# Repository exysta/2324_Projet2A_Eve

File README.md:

# Project Eve

<div align="center">

<br>

[Code](Code/) 
| [Documentation](Documents/) 
| [Liens utiles](Documents/Liens_utiles.md) 
| [Journal](Journal/ReadMe.md)
| [Bilan des présentations](Présentation/ReadMe.md)

</div>

## Introduction

Vous vous situez sur le Github d'Eve (anciennement Robourt). C'est un projet de bras robotique six axes réalisé par des étudiants de l'ENSEA. Vous pourrez trouver ici la documentation, le guide d'utilisation, le journal de bord (et autres documents connexes) pour comprendre notre projet. Nous vous souhaitons une bonne lecture !

> You are in the Github of Eve (formely Robourt). This is a project of a six-axis robot arm project by students at ENSEA. Here you can find here documentation, user guide, logbook (and other related documents) to help you understand our project. We hope you enjoy reading! The rest of the text will be in French exclusively.

### Table des matières

1. [Partie Software](#partie-software)
2. [Partie Hardware et intégration](#partie-hardware-et-intégration)
3. [Guide d'utilisation](#guide-dutilisation)
4. [Annexes](#annexes)

## Partie-Software

### Contrôle des servos moteurs avec Dynamixel 2.0

Dans le cadre du projet, les servomoteurs servent à actionner la pince et à gérer certains axes de rotation du robot ne nécessitant pas beaucoup de couple. Il y a un total de 4 servomoteurs, tous utilisant le protocole Dynamixel 2.0 et connectés en série. Nous utilisons une connexion UART en mode half-duplex avec notre microprocesseur.

#### Connexion UART Half-Duplex

Il est nécessaire de configurer le GPIO utilisé pour l'UART en mode open drain avec une résistance de pull-up pour que le half-duplex puisse fonctionner.
<div align="center">
<br>
 </br>
Extrait du reference manual </br>
</br> 
</div>

Pour envoyer et recevoir des données, il est nécessaire de préciser si l'on transmet ou reçoit pour éviter les conflits sur le fil unique utilisé pour l'UART. Pour cela, on utilise les fonctions HAL correspondantes HAL_HalfDuplex_EnableTransmitter() et HAL_HalfDuplex_EnableReceiver().

#### Protocole Dynamixel 2.0

La majorité des informations ont été obtenues sur cette page https://emanual.robotis.com/docs/en/dxl/protocol2/

### Contrôle des steppers par la TMC2590

#### Connexion SPI

On doit configurer SPI1 avec 3 ports MISO/MOSI & CLK (configurable dans IOC) et un Chip Select Not. Pour asservir un driver, il faut mettre son bit en état bas (ce qui a été fait dans l'initialisation du code).
Le but est de transmettre un mot en bits contenant l'ordre (angles en degré) et la configuration du TMC2590. 

Pour cela nous avons la possibilité d'écrire dans 5 registres différents

<div align="center">
<br>
 </br>
Registres </br>
</br> 
</div>

<div align="center">
<br>
 </br>
Formats des registres </br>
</br> 
</div>

On remarque alors que ce sont les 2 bits de poids fort qui détermine dans quels registres nous écrivons.  Nous modifierons uniquement 2 registres : DRVCTRL & DRVCON. Nous laisserons les autres registres aux valeurs par défaut (mais nous pourrons les configurer à besoin si nécessaire).

##### Registre DRVCTRL

C'est le registre qui fait décide du courant à envoyer dans le stepper.

<div align="center">
<br>
 </br>
Formats du registre DRVCTRL en mode SPI </br>
</br> 
</div>

Pour commander les steppers, il faut leur envoyer des amplitudes de courant. Il faut donc trouver une relation entre les angles et le courant. Nous avons trouvé une relation entre les deux avec un sinus. __A expliquer__

On sait que le courant correspond à la partie entière du sinus(angle) * 255. On stocke ensuite toutes ces données dans un tableau qui fait des ordres de 0 à 90°. Comme le sinus est périodique, cela suffira à faire n'importe quel calcul de sinus/cosinus.

##### Registre DRVCONF

C'est le registre qui configure le driver.

<div align="center">
<br>
 </br>
Formats du registre DRVCONF </br>
</br> 
</div>

C'est ici qu'il faut modfier le bit pour désactiver l'interface STEP/DIR. Pour choisir le mode SPI il faut que le bit SDOFF soit égal à 1. Sinon, l'interface choisie sera STEP/DIR.

Il faudra aussi modifier les bits 4&5 pour configurer une partie de la réponse (voir image suivante).

##### Les registres pour la réponse

Nous pouvons aussi récupérer des informations à l'aide d'autres registres uniquement en lecture.

<div align="center">
<br>
 </br>
Formats des registres de réponse </br>
</br> 
</div>

Nous avons donc configuré les registres avec les paramètres suivants :

```c
	phtmc2590->drvCtrlRegister 			= 0x00000; // No Current
	phtmc2590->chopConfRegister			= 0b10011000000000001111; // 100 10
	phtmc2590->smartEnRegister 			= 0b10100000000000000000; // 101 0
	phtmc2590->stallGuardCtrlRegister 	= 0b11000000000000011111;//0xD001F; // 110 1---- 11111
	phtmc2590->drvConfRegister 			= 0b11100000011110110000;//0xE0480; // 1110 0000 0100 1000 0000
```

#### Explication du code

Nous sommes passé par une structure
Le code de commande pour la TMC2590 est séparé en plusieurs parties : 

* tmc2590_Init : Permet d'initialiser les registres du driver et de le mettre prêt au fonctionnement. Pour le moment, l'activation du signal nCS se fait à ce moment mais par la suite, il sera fait dans une autre fonction qui décidera avec quel stepper on communique.

```c
void tmc2590_Init(TMC2590_HandleTypeDef *phtmc2590, SPI_HandleTypeDef *hspi, GPIO_TypeDef *gpioPortNCS, uint16_t gpioPinNCS, GPIO_TypeDef *gpioPortDrvEnN, uint16_t gpioPinDrvEnN){
	uint8_t pData[3];
	phtmc2590->hspi = hspi;
	phtmc2590->gpioPinNCS = gpioPinNCS;
	phtmc2590->gpioPortNCS = gpioPortNCS;
	phtmc2590->gpioPinDrvEnN = gpioPinDrvEnN;
	phtmc2590->gpioPortDrvEnN = gpioPortDrvEnN;

	tmc2590_SetPowerEnable(phtmc2590, SET);
	tmc2590_SetnCS(phtmc2590, SET);

	phtmc2590->drvCtrlRegister 			= 0x00000; // No Current
	phtmc2590->chopConfRegister			= 0b10011000000000001111; // 100 10
	phtmc2590->smartEnRegister 			= 0b10100000000000000000; // 101 0
	phtmc2590->stallGuardCtrlRegister 	= 0b11000000000000011111;//0xD001F; // 110 1---- 11111
	phtmc2590->drvConfRegister 			= 0b11100000011110110000;//0xE0480; // 1110 0000 0100 1000 0000

	tmc2590_SetTxBufferInt32(phtmc2590, phtmc2590->drvCtrlRegister);
	tmc2590_TransmitReceive(phtmc2590, TMC2590_CMD_SIZE);
	tmc2590_SetTxBufferInt32(phtmc2590, phtmc2590->chopConfRegister);
	tmc2590_TransmitReceive(phtmc2590, TMC2590_CMD_SIZE);
	tmc2590_SetTxBufferInt32(phtmc2590, phtmc2590->smartEnRegister);
	tmc2590_TransmitReceive(phtmc2590, TMC2590_CMD_SIZE);
	tmc2590_SetTxBufferInt32(phtmc2590, phtmc2590->stallGuardCtrlRegister);
	tmc2590_TransmitReceive(phtmc2590, TMC2590_CMD_SIZE);
	tmc2590_SetTxBufferInt32(phtmc2590, phtmc2590->drvConfRegister);
	tmc2590_TransmitReceive(phtmc2590, TMC2590_CMD_SIZE);

	HAL_TIM_Base_Start_IT(&htim2);

}
```
<div align="center">
Code tmc2590_Init </br>
</br> 
</div>

Entrées : 
* Structure TMC2590
* Pointeur SPI
* Signal nCS
* Pin nCS
* Signal DRVENN
* Pin DRVENN

* sendOrderStepper : 

```c
int sendOrderStepper(int inputOrder){

	/*
	 * We need to put in input how much we want to turn in degrees and what stepper we want to move
	 * For the moment, we have only one stepper but with nCS signal, we will be able to change with
	 * stepper we want to communicate
	 */
	int polarity = (inputOrder>0);
	int order = (int) abs(inputOrder)*142.2;
	int indice = 0;
	while (indice != order){
		uint32_t stateInterruption = HAL_GPIO_ReadPin(GPIOC, GPIO_PIN_8);
		if (stateInterruption != 0){
			return 0;
		}
		if(perioedElapsed_IT){
				if(index_sin_loop < 256){
					currentCoilA = sinTable[index_sin_loop];
					currentCoilB = sinTable[256-index_sin_loop];
					polarityCoilA = polarity;
					polarityCoilB = 1;
				}
				else if(index_sin_loop < 512){
					currentCoilA = sinTable[512-index_sin_loop];
					currentCoilB = sinTable[index_sin_loop-256];
					polarityCoilA = polarity;
					polarityCoilB = 0;
				}
				else if(index_sin_loop < 768){
					currentCoilA = sinTable[index_sin_loop-512];
					currentCoilB = sinTable[768-index_sin_loop];
					polarityCoilA = 1 - polarity;
					polarityCoilB = 0;
				}
				else{
					currentCoilA = sinTable[1024-index_sin_loop];
					currentCoilB = sinTable[index_sin_loop-768];
					polarityCoilA = 1 - polarity;
					polarityCoilB = 1;
				}
				index_sin_loop = (index_sin_loop+1)%1024;
				indice++;

				drvCtrlCommand = (polarityCoilA << 17) | (currentCoilA << 9) | (polarityCoilB << 8) | (currentCoilB << 0);
				tmc2590_SetTxBufferInt32(&htmc2590, drvCtrlCommand);
				tmc2590_TransmitReceive(&htmc2590, TMC2590_CMD_SIZE);
				perioedElapsed_IT = 0;
			}
	}
	return 1;

```

<div align="center">
Code sendOrderStepper </br>
</div>

### ROS 2

Il y a deux manières de faire avec ROS2 :
* ROS2 contrôle tout : le contrôle, la gestion des ressources et les calculs => Utilisation de [ROS_Control](https://github.com/ros-controls/control.ros.org) (Méthode 1)
* ROS2 ne fait presque rien : Il transmet simplement les données d'un point A à un point B (Méthode 2)

<div align="center">
<br>
 </br>
Schéma de la méthode 1 </br>
</br> 
</div>

Le problème avec la méthode 1, c'est que comme tout est géré par ROS, on n'utilise pas la STM32 et donc notre projet d'électronique n'a plus de sens. Autre problème de la méthode 1, c'est l'utilisation de C++ pour faire le code qui est un langage POO assez complexe à prendre en main alors que tous les packages étaient actuellement fait sous python.

La 2e méthode revient à créer une entrée où l'on mettra les ordres (des angles pour différents moteurs) puis tout est envoyé par UART à la STM32 qui effectue l'envoi des ordre pour chacun des moteurs. 

C'est plutôt la 2e méthode qui est envisagée étant donnée que le groupe de 3e année ont réalisé une simulation qui permet de passer de coordonnées x,y & z en données d'angles pour chaque moteur. On aurait alors à transmettre ces données à la carte STM32 (UART) qui s'occuperait de la partie commande des moteurs.

Il faut définir le protocole de communication entre les deux appareils en s'inspirant du Dynamixel.

## Partie Hardware et intégration

### Cahier des charges - Matériel

* TMC2590
* 17hs19-2004s
* XL320 (x2)
* XL430 w250 (x2)
* 23HS8430
* 23hS2442B Nema 23
* STM32 L412
* BU33SD5WG-TR

<div align="center">

</div>

## Annexes

Diagramme de Gantt

<div align="center">
 </br>
</div>

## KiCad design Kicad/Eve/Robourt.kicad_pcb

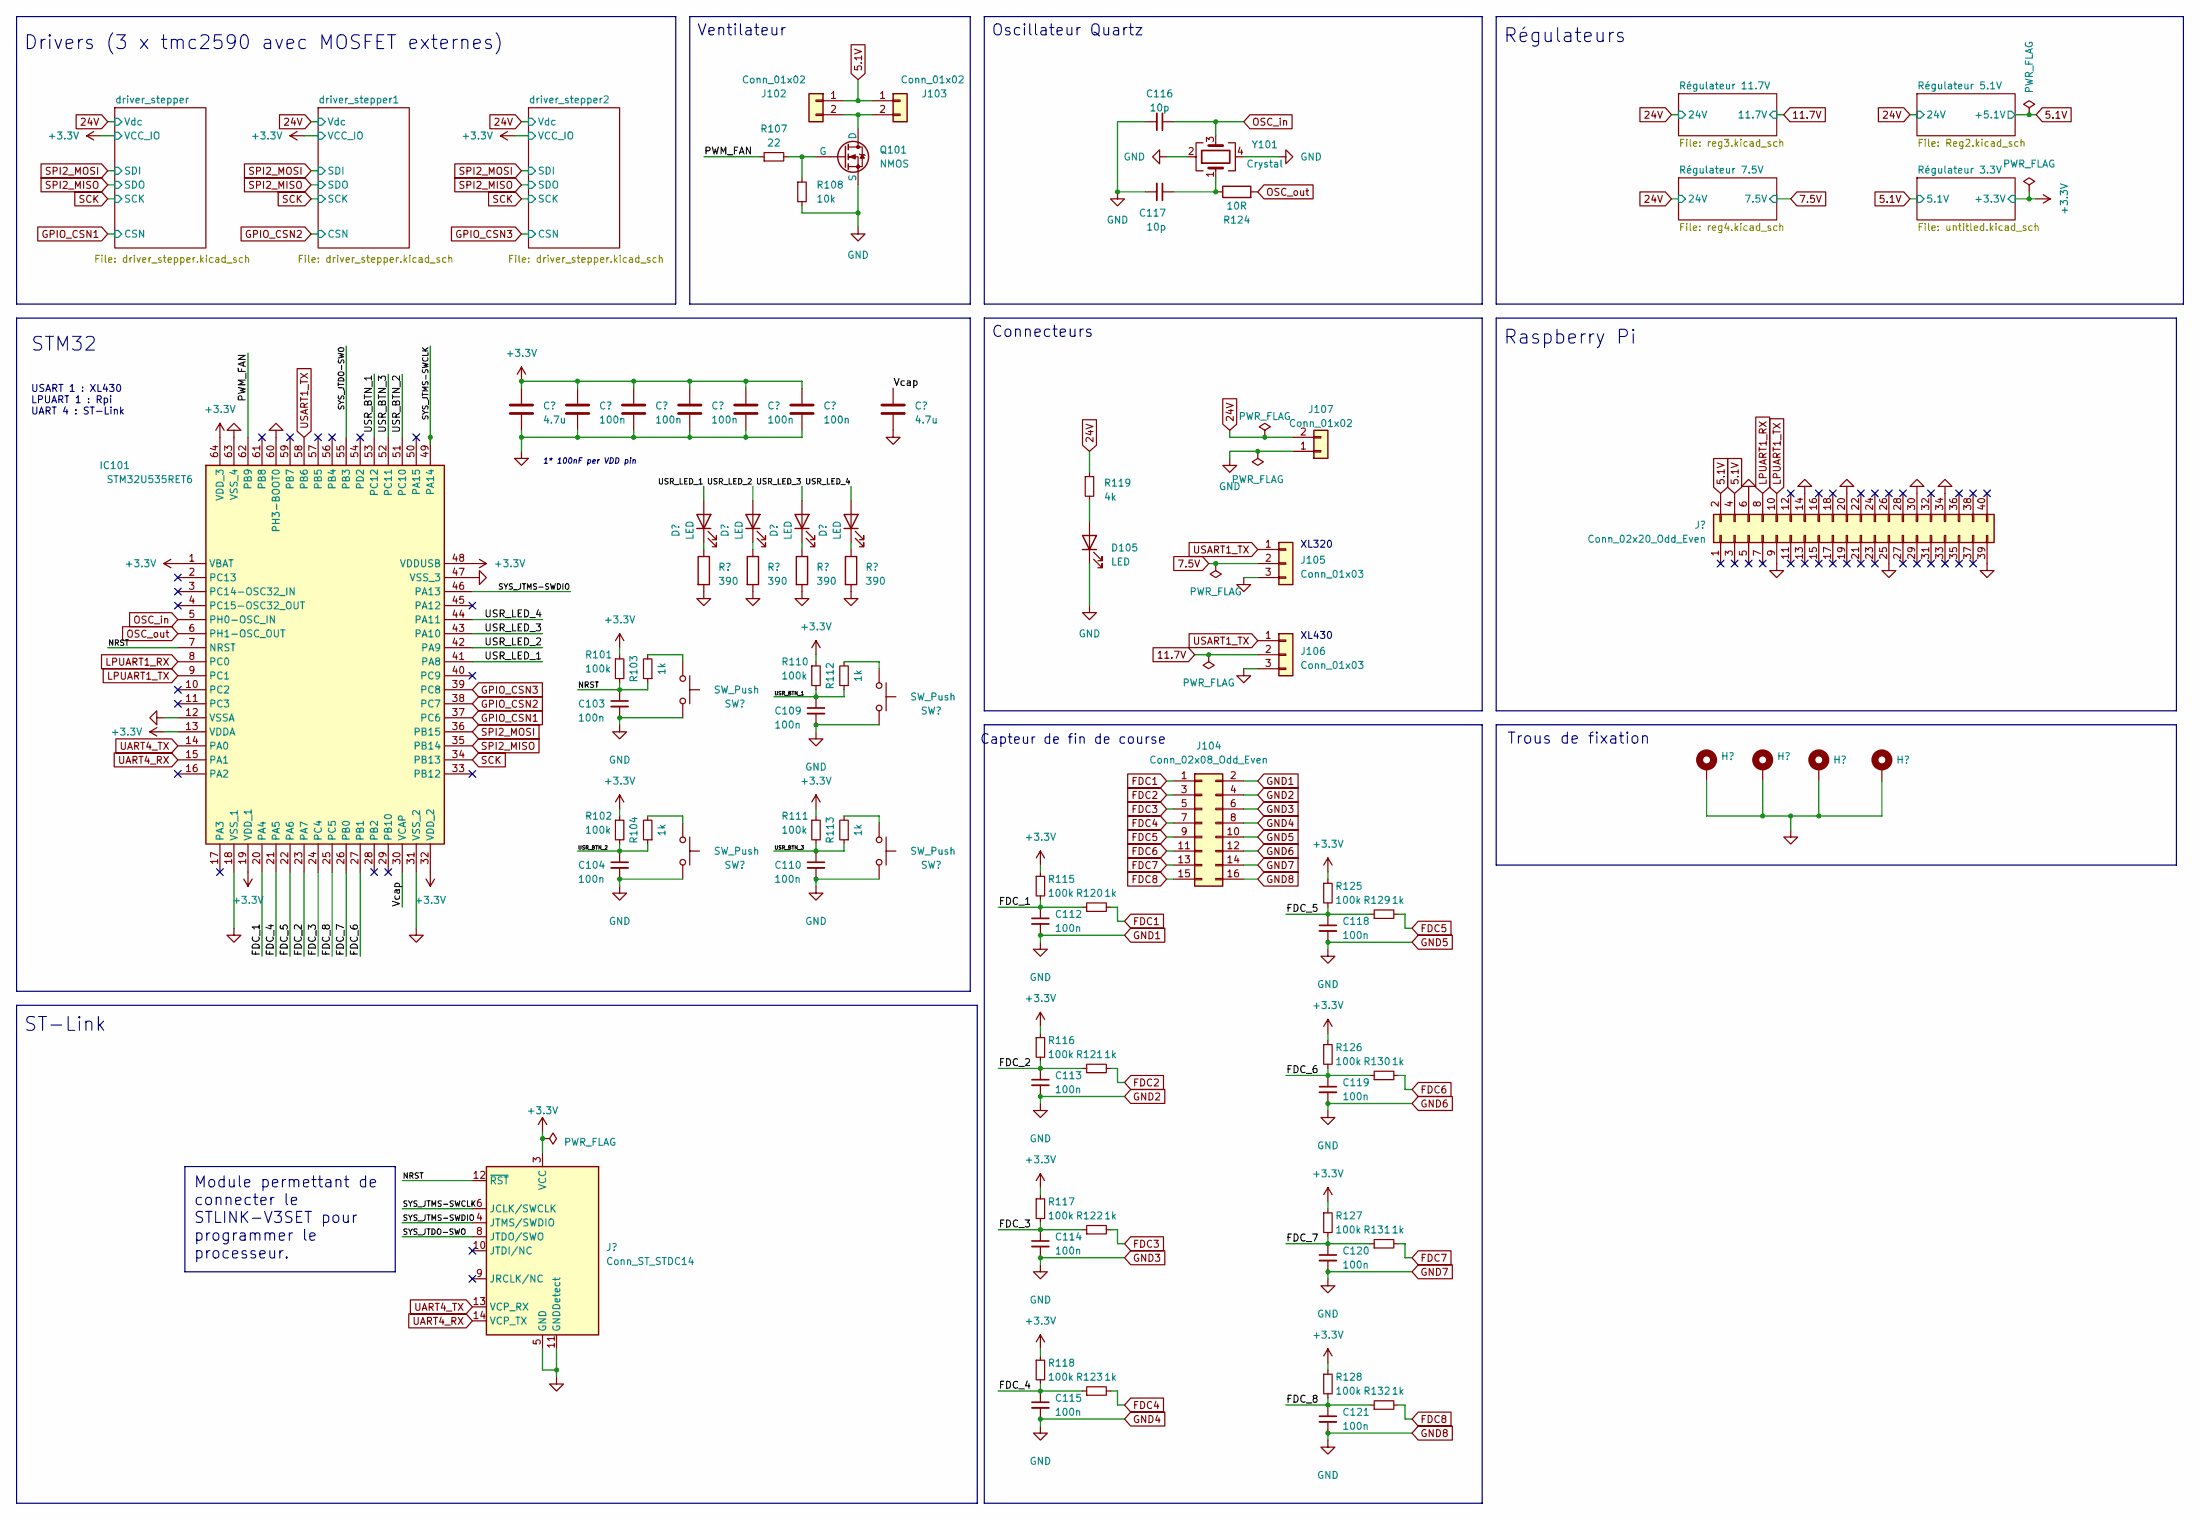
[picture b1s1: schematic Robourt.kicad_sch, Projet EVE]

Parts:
C101, C111: 4.7u; C_0402_1005Metric
C102, C103, C104, C105, C106, C107, C108, C109, C110, C112, C113, C114, C115, C118, C119, C120, C121: 100n; C_0402_1005Metric
C116, C117: 10p; C_0402_1005Metric
D101, D102, D103, D104, D105: LED; LED_0603_1608Metric
H101, H102, H103, H104: MountingHole_Pad; MountingHole_3.2mm_M3_Pad_Via
IC101: STM32U535RET6; QFP50P1200X1200X160-64N; Mouser Part Number 511-STM32U535RET6
J101: Conn_ST_STDC14; PinHeader_2x07_P1.27mm_Vertical_SMD
J102, J103: Conn_01x02; JST_XH_B2B-XH-A_1x02_P2.50mm_Vertical
J104: Conn_02x08_Odd_Even; PinHeader_2x08_P2.00mm_Vertical_SMD
J105, J106: Conn_01x03; JST_XH_B3B-XH-A_1x03_P2.50mm_Vertical
J107: Conn_01x02; AMASS_XT60-F_1x02_P7.20mm_Vertical
J108: Conn_02x20_Odd_Even; PinSocket_2x20_P2.54mm_Horizontal
Q101: NMOS; SOT-23
R101, R102, R110, R111, R115, R116, R117, R118, R125, R126, R127, R128: 100k; R_0402_1005Metric
R103, R104, R112, R113, R120, R121, R122, R123, R129, R130, R131, R132: 1k; R_0402_1005Metric
R105, R106, R109, R114: 390; R_0402_1005Metric
R107: 22; R_0402_1005Metric
R108: 10k; R_0402_1005Metric
R119: 4k; R_0402_1005Metric
R124: 10R; R_0402_1005Metric
SW101, SW102, SW103, SW104: SW_Push; SW_SPST_B3U-1000P
Y101: Crystal; Crystal_SMD_EuroQuartz_MT-4Pin_3.2x2.5mm

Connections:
24V: J107.2, R119.1; also elsewhere on the board
+3.3V: C101.1, C102.1, C105.1, C106.1, C107.1, C108.1, IC101.1 (VBAT), IC101.13 (VDDA), IC101.19 (VDD_1), IC101.32 (VDD_2), IC101.48 (VDDUSB), IC101.64 (VDD_3), J101.3 (VCC), R101.1, R102.1, R110.1, R111.1, R115.1, R116.1, R117.1, R118.1, R125.1, R126.1, R127.1, R128.1; also elsewhere on the board
/FDC_1: C112.1, IC101.20 (PA4), R115.2, R120.1
/FDC_2: C113.1, IC101.23 (PA7), R116.2, R121.1
/FDC_3: C114.1, IC101.24 (PC4), R117.2, R122.1
/FDC_4: C115.1, IC101.21 (PA5), R118.2, R123.1
/FDC_5: C118.1, IC101.22 (PA6), R125.2, R129.1
/FDC_6: C119.1, IC101.27 (PB1), R126.2, R130.1
/FDC_7: C120.1, IC101.26 (PB0), R127.2, R131.1
/FDC_8: C121.1, IC101.25 (PC5), R128.2, R132.1
/NRST: C103.1, IC101.7 (NRST), J101.12 (~RST), R101.2, R103.1
/PWM_FAN: IC101.62 (PB9), R107.1
/SYS_JTDO-SWO: IC101.55 (PB3), J101.8 (JTDO/SWO)
/SYS_JTMS-SWCLK: IC101.49 (PA14), J101.6 (JCLK/SWCLK)
/SYS_JTMS-SWDIO: IC101.46 (PA13), J101.4 (JTMS/SWDIO)
/USR_BTN_1: C109.1, IC101.53 (PC12), R110.2, R112.1
/USR_BTN_2: C104.1, IC101.51 (PC10), R102.2, R104.1
/USR_BTN_3: C110.1, IC101.52 (PC11), R111.2, R113.1
/USR_LED_1: D101.2 (A), IC101.41 (PA8)
/USR_LED_2: D102.2 (A), IC101.42 (PA9)
/USR_LED_3: D103.2 (A), IC101.43 (PA10)
/USR_LED_4: D104.2 (A), IC101.44 (PA11)
/Vcap: C111.1, IC101.30 (VCAP)
FDC1: J104.1, R120.2; also elsewhere on the board
FDC2: J104.3, R121.2; also elsewhere on the board
FDC3: J104.5, R122.2; also elsewhere on the board
FDC4: J104.7, R123.2; also elsewhere on the board
FDC5: J104.9, R129.2; also elsewhere on the board
FDC6: J104.11, R130.2; also elsewhere on the board
FDC7: J104.13, R131.2; also elsewhere on the board
FDC8: J104.15, R132.2; also elsewhere on the board
GND1: C101.2, C102.2, C103.2, C104.2, C105.2, C106.2, C107.2, C108.2, C109.2, C110.2, C111.2, C112.2, C113.2, C114.2, C115.2, C116.2, C117.2, C118.2, C119.2, C120.2, C121.2, D105.1 (K), H101.1, H102.1, H103.1, H104.1, IC101.12 (VSSA), IC101.18 (VSS_1), IC101.31 (VSS_2), IC101.47 (VSS_3), IC101.60 (PH3-BOOT0), IC101.63 (VSS_4), J101.5 (GND), J101.7 (GND), J101.11 (GNDDetect), J104.2, J104.4, J104.6, J104.8, J104.10, J104.12, J104.14, J104.16, J105.3, J106.3, J107.1, J108.3, J108.6, J108.9, J108.14, J108.20, J108.25, J108.30, J108.34, J108.39, Q101.3 (S), R105.2, R106.2, R108.2, R109.2, R114.2, SW101.2, SW102.2, SW103.2, SW104.2, Y101.2, Y101.4; also elsewhere on the board
GPIO_CSN1: IC101.37 (PC6); also elsewhere on the board
GPIO_CSN2: IC101.38 (PC7); also elsewhere on the board
GPIO_CSN3: IC101.39 (PC8); also elsewhere on the board
LPUART1_RX: IC101.8 (PC0), J108.8; also elsewhere on the board
LPUART1_TX: IC101.9 (PC1), J108.10; also elsewhere on the board
unnamed: C117.1, R124.1, Y101.1
unnamed: D101.1 (K), R105.1
unnamed: D102.1 (K), R106.1
unnamed: D103.1 (K), R109.1
unnamed: D104.1 (K), R114.1
unnamed: D105.2 (A), R119.2
unnamed: J102.2, J103.2, Q101.1 (D)
unnamed: Q101.2 (G), R107.2, R108.1
unnamed: R103.2, SW101.1
unnamed: R104.2, SW102.1
unnamed: R112.2, SW103.1
unnamed: R113.2, SW104.1
OSC_in: C116.1, IC101.5 (PH0-OSC_IN), Y101.3
OSC_out: IC101.6 (PH1-OSC_OUT), R124.2
SCK: IC101.34 (PB13); also elsewhere on the board
SPI2_MISO: IC101.35 (PB14); also elsewhere on the board
SPI2_MOSI: IC101.36 (PB15); also elsewhere on the board
UART4_RX: IC101.15 (PA1), J101.14 (VCP_TX)
UART4_TX: IC101.14 (PA0), J101.13 (VCP_RX)
USART1_TX: IC101.58 (PB6), J105.1, J106.1, J108.1; also elsewhere on the board

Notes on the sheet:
Module permettant de connecter le STLINK-V3SET pour programmer le processeur.
Capteur de fin de course
Drivers (3 x tmc2590 avec MOSFET externes)
XL430
Connecteurs
XL320
STM32
Trous de fixation
USART 1 : XL430 LPUART 1 : Rpi UART 4 : ST-Link
Régulateurs
ST-Link
Oscillateur Quartz
Raspberry Pi
Ventilateur
1* 100nF per VDD pin

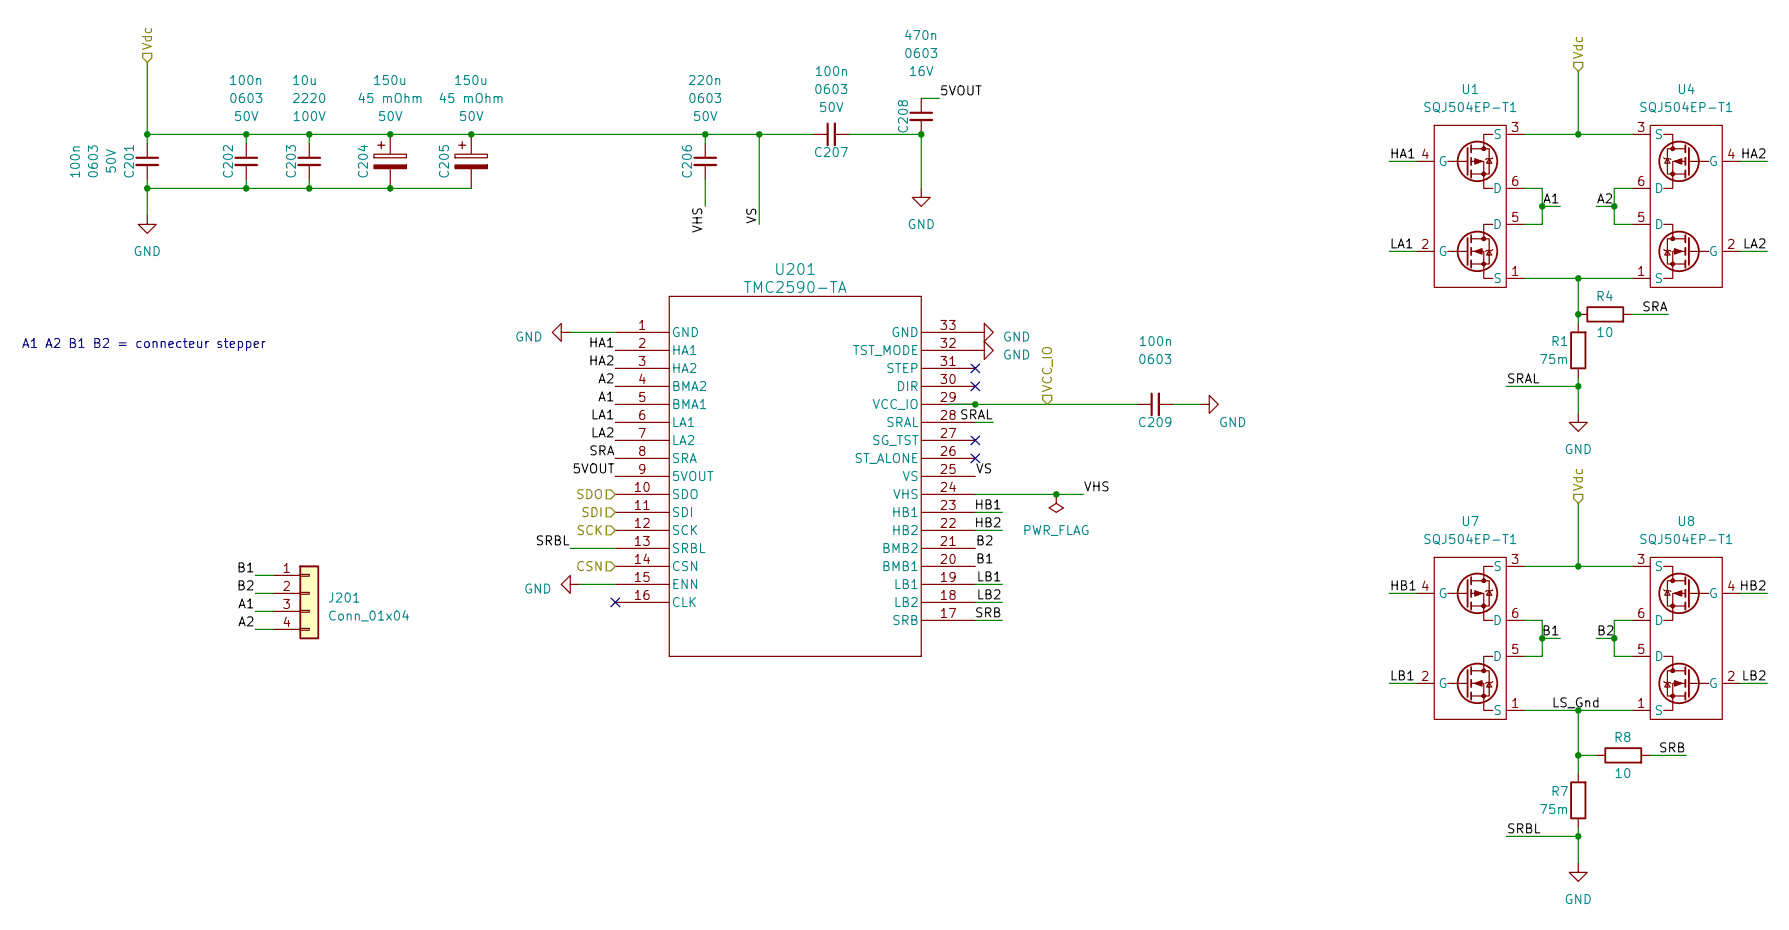
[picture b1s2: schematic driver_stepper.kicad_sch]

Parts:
C201, C202, C207: 100n; C_0402_1005Metric; Voltage 50V
C203: 10u; C_2220_5750Metric; Voltage 100V
C204, C205: 150u; CP_Elec_10x10.5; Voltage 50V
C206: 220n; C_0402_1005Metric; Voltage 50V
C208: 470n; C_0402_1005Metric; Voltage 16V
C209: 100n; C_0402_1005Metric; Voltage 16V
J201: Conn_01x04; Molex_Mini-Fit_Jr_5566-04A_2x02_P4.20mm_Vertical
R1, R7: 75m; R_2512_6332Metric
R4, R8: 10; R_0402_1005Metric; Tolerance 1%
U1, U4, U7, U8: SQJ504EP-T1; SQJ968EPT1GE3
U201: TMC2590-TA; QFP50P700X700X114-33N

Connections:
24V: C201.1, C202.1, C203.1, C204.1, C205.1, C206.1, C207.1, U1.3 (S), U4.3 (S), U7.3 (S), U8.3 (S), U201.25 (VS); also elsewhere on the board
+3.3V: C209.1, U201.29 (VCC_IO); also elsewhere on the board
/driver_stepper/5VOUT: C208.1, U201.9 (5VOUT)
/driver_stepper/A1: J201.3, U1.5 (D), U1.6 (D), U201.5 (BMA1)
/driver_stepper/A2: J201.4, U4.5 (D), U4.6 (D), U201.4 (BMA2)
/driver_stepper/B1: J201.1, U7.5 (D), U7.6 (D), U201.20 (BMB1)
/driver_stepper/B2: J201.2, U8.5 (D), U8.6 (D), U201.21 (BMB2)
/driver_stepper/HA1: U1.4 (G), U201.2 (HA1)
/driver_stepper/HA2: U4.4 (G), U201.3 (HA2)
/driver_stepper/HB1: U7.4 (G), U201.23 (HB1)
/driver_stepper/HB2: U8.4 (G), U201.22 (HB2)
/driver_stepper/LA1: U1.2 (G), U201.6 (LA1)
/driver_stepper/LA2: U4.2 (G), U201.7 (LA2)
/driver_stepper/LB1: U7.2 (G), U201.19 (LB1)
/driver_stepper/LB2: U8.2 (G), U201.18 (LB2)
/driver_stepper/LS_Gnd: R7.2, R8.1, U7.1 (S), U8.1 (S)
/driver_stepper/SRA: R4.2, U201.8 (SRA)
/driver_stepper/SRB: R8.2, U201.17 (SRB)
/driver_stepper/VHS: C206.2, U201.24 (VHS)
GND1: C201.2, C202.2, C203.2, C204.2, C205.2, C207.2, C208.2, C209.2, R1.1, R7.1, U201.1 (GND), U201.13 (SRBL), U201.15 (ENN), U201.28 (SRAL), U201.32 (TST_MODE), U201.33 (GND); also elsewhere on the board
GPIO_CSN1: U201.14 (CSN); also elsewhere on the board
unnamed: R1.2, R4.1, U1.1 (S), U4.1 (S)
SCK: U201.12 (SCK); also elsewhere on the board
SPI2_MISO: U201.10 (SDO); also elsewhere on the board
SPI2_MOSI: U201.11 (SDI); also elsewhere on the board

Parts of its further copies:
C301, C302, C307, C401, C402, C407: 100n; C_0402_1005Metric; Voltage 50V
C303, C403: 10u; C_2220_5750Metric; Voltage 100V
C304, C305, C404, C405: 150u; CP_Elec_10x10.5; Voltage 50V
C306, C406: 220n; C_0402_1005Metric; Voltage 50V
C308, C408: 470n; C_0402_1005Metric; Voltage 16V
C309, C409: 100n; C_0402_1005Metric; Voltage 16V
J301, J401: Conn_01x04; Molex_Mini-Fit_Jr_5566-04A_2x02_P4.20mm_Vertical
R2, R3, R9, R11: 75m; R_2512_6332Metric
R5, R6, R10, R12: 10; R_0402_1005Metric; Tolerance 1%
U2, U3, U5, U6, U9, U10, U11, U12: SQJ504EP-T1; SQJ968EPT1GE3
U301, U401: TMC2590-TA; QFP50P700X700X114-33N

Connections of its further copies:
24V: C301.1, C302.1, C303.1, C304.1, C305.1, C306.1, C307.1, C401.1, C402.1, C403.1, C404.1, C405.1, C406.1, C407.1, U2.3 (S), U3.3 (S), U5.3 (S), U6.3 (S), U9.3 (S), U10.3 (S), U11.3 (S), U12.3 (S), U301.25 (VS), U401.25 (VS); also elsewhere on the board
+3.3V: C309.1, C409.1, U301.29 (VCC_IO), U401.29 (VCC_IO); also elsewhere on the board
/driver_stepper1/5VOUT: C308.1, U301.9 (5VOUT)
/driver_stepper1/A1: J301.3, U2.5 (D), U2.6 (D), U301.5 (BMA1)
/driver_stepper1/A2: J301.4, U5.5 (D), U5.6 (D), U301.4 (BMA2)
/driver_stepper1/B1: J301.1, U9.5 (D), U9.6 (D), U301.20 (BMB1)
/driver_stepper1/B2: J301.2, U10.5 (D), U10.6 (D), U301.21 (BMB2)
/driver_stepper1/HA1: U2.4 (G), U301.2 (HA1)
/driver_stepper1/HA2: U5.4 (G), U301.3 (HA2)
/driver_stepper1/HB1: U9.4 (G), U301.23 (HB1)
/driver_stepper1/HB2: U10.4 (G), U301.22 (HB2)
/driver_stepper1/LA1: U2.2 (G), U301.6 (LA1)
/driver_stepper1/LA2: U5.2 (G), U301.7 (LA2)
/driver_stepper1/LB1: U9.2 (G), U301.19 (LB1)
/driver_stepper1/LB2: U10.2 (G), U301.18 (LB2)
/driver_stepper1/LS_Gnd: R9.2, R10.1, U9.1 (S), U10.1 (S)
/driver_stepper1/SRA: R5.2, U301.8 (SRA)
/driver_stepper1/SRB: R10.2, U301.17 (SRB)
/driver_stepper1/VHS: C306.2, U301.24 (VHS)
/driver_stepper2/5VOUT: C408.1, U401.9 (5VOUT)
/driver_stepper2/A1: J401.3, U3.5 (D), U3.6 (D), U401.5 (BMA1)
/driver_stepper2/A2: J401.4, U6.5 (D), U6.6 (D), U401.4 (BMA2)
/driver_stepper2/B1: J401.1, U11.5 (D), U11.6 (D), U401.20 (BMB1)
/driver_stepper2/B2: J401.2, U12.5 (D), U12.6 (D), U401.21 (BMB2)
/driver_stepper2/HA1: U3.4 (G), U401.2 (HA1)
/driver_stepper2/HA2: U6.4 (G), U401.3 (HA2)
/driver_stepper2/HB1: U11.4 (G), U401.23 (HB1)
/driver_stepper2/HB2: U12.4 (G), U401.22 (HB2)
/driver_stepper2/LA1: U3.2 (G), U401.6 (LA1)
/driver_stepper2/LA2: U6.2 (G), U401.7 (LA2)
/driver_stepper2/LB1: U11.2 (G), U401.19 (LB1)
/driver_stepper2/LB2: U12.2 (G), U401.18 (LB2)
/driver_stepper2/LS_Gnd: R11.2, R12.1, U11.1 (S), U12.1 (S)
/driver_stepper2/SRA: R6.2, U401.8 (SRA)
/driver_stepper2/SRB: R12.2, U401.17 (SRB)
/driver_stepper2/VHS: C406.2, U401.24 (VHS)
GND1: C301.2, C302.2, C303.2, C304.2, C305.2, C307.2, C308.2, C309.2, C401.2, C402.2, C403.2, C404.2, C405.2, C407.2, C408.2, C409.2, R2.1, R3.1, R9.1, R11.1, U301.1 (GND), U301.13 (SRBL), U301.15 (ENN), U301.28 (SRAL), U301.32 (TST_MODE), U301.33 (GND), U401.1 (GND), U401.13 (SRBL), U401.15 (ENN), U401.28 (SRAL), U401.32 (TST_MODE), U401.33 (GND); also elsewhere on the board
GPIO_CSN2: U301.14 (CSN); also elsewhere on the board
GPIO_CSN3: U401.14 (CSN); also elsewhere on the board
unnamed: R2.2, R5.1, U2.1 (S), U5.1 (S)
unnamed: R3.2, R6.1, U3.1 (S), U6.1 (S)
SCK: U301.12 (SCK), U401.12 (SCK); also elsewhere on the board
SPI2_MISO: U301.10 (SDO), U401.10 (SDO); also elsewhere on the board
SPI2_MOSI: U301.11 (SDI), U401.11 (SDI); also elsewhere on the board

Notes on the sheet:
A1 A2 B1 B2 = connecteur stepper

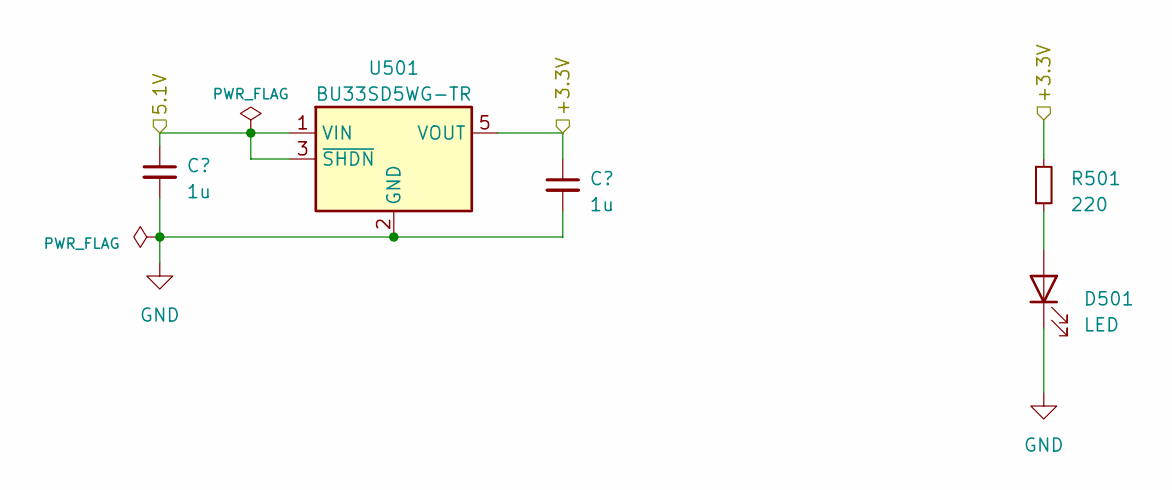
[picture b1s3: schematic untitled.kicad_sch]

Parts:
C501, C502: 1u; C_0402_1005Metric
D501: LED; LED_0603_1608Metric
R501: 220; R_0402_1005Metric
U501: BU33SD5WG-TR; SOT-23-5

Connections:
+3.3V: C502.1, R501.1, U501.5 (VOUT); also elsewhere on the board
GND1: C501.2, C502.2, D501.1 (K), U501.2 (GND); also elsewhere on the board
unnamed: D501.2 (A), R501.2

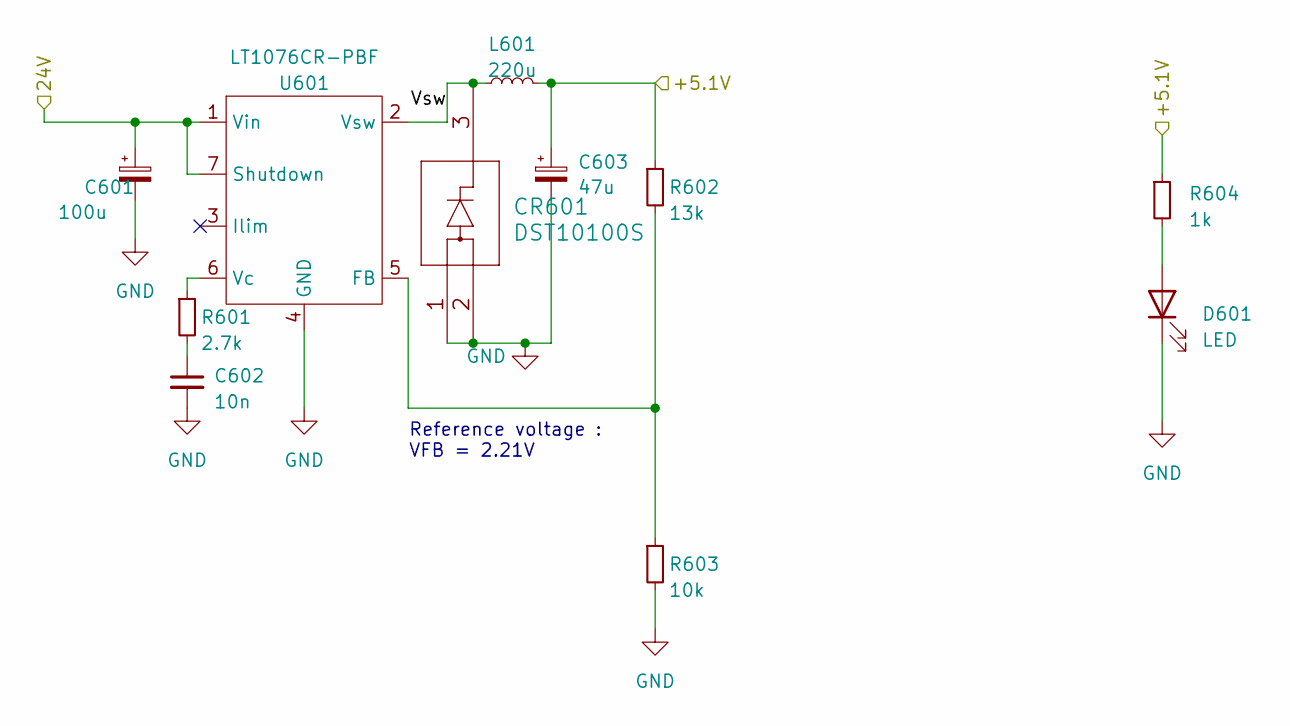
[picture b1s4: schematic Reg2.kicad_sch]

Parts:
C601: 100u; CP_Elec_6.3x7.7
C602: 10n; C_0402_1005Metric
C603: 47u; CP_Elec_6.3x5.4
CR601: DST10100S
D601: LED; LED_0603_1608Metric
L601: 220u; L_Changjiang_FNR8065S
R601: 2.7k; R_0402_1005Metric
R602: 13k; R_0402_1005Metric
R603: 10k; R_0402_1005Metric
R604: 1k; R_0402_1005Metric
U601: LT1076CR-PBF

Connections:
24V: C601.1, U601.1 (Vin), U601.7 (Shutdown); also elsewhere on the board
/Régulateur 5.1V/Vsw: CR601.3, L601.1, U601.2 (Vsw)
GND1: C601.2, C602.2, C603.2, CR601.1, CR601.2, D601.1 (K), R603.2, U601.4 (GND); also elsewhere on the board
unnamed: C602.1, R601.2
unnamed: D601.2 (A), R604.2
unnamed: R602.2, R603.1, U601.5 (FB)
unnamed: R601.1, U601.6 (Vc)

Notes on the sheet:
Reference voltage : VFB = 2.21V

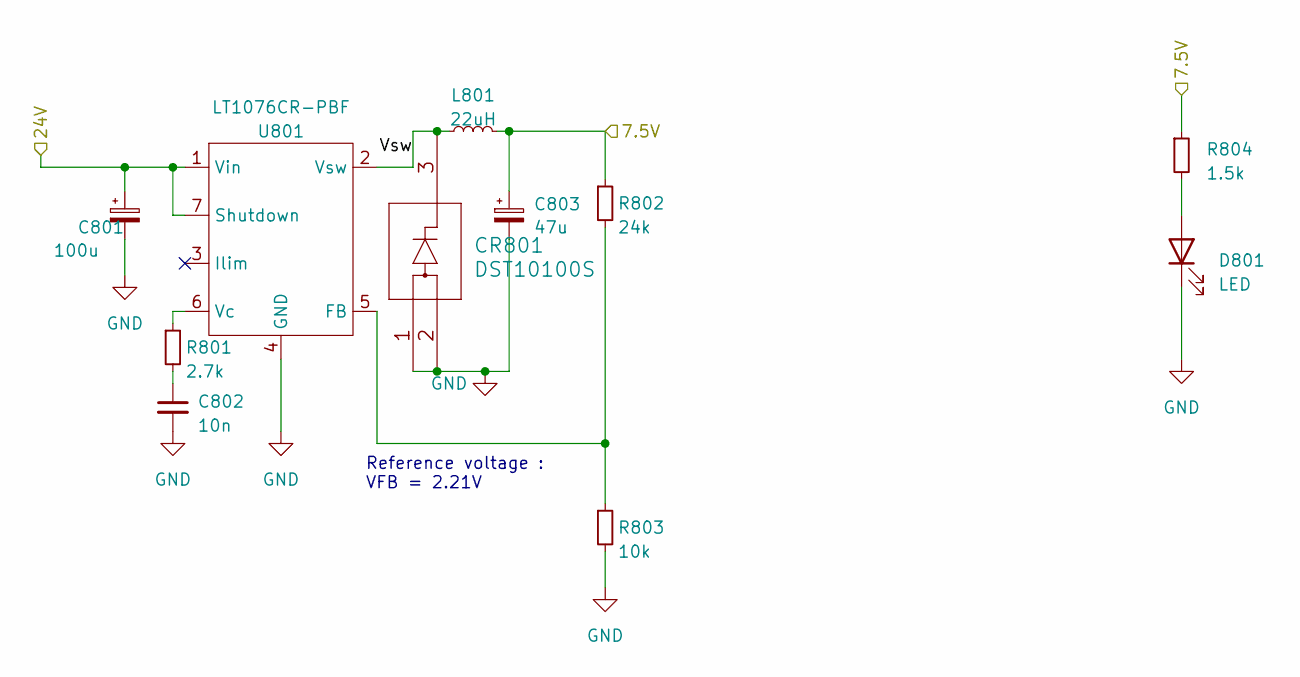
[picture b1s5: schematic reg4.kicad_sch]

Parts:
C801: 100u; CP_Elec_6.3x7.7
C802: 10n; C_0402_1005Metric
C803: 47u; CP_Elec_6.3x5.4
CR801: DST10100S
D801: LED; LED_0603_1608Metric
L801: 22uH; L_Changjiang_FNR8065S
R801: 2.7k; R_0402_1005Metric
R802: 24k; R_0402_1005Metric
R803: 10k; R_0402_1005Metric
R804: 1.5k; R_0402_1005Metric
U801: LT1076CR-PBF

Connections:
24V: C801.1, U801.1 (Vin), U801.7 (Shutdown); also elsewhere on the board
/Régulateur 7.5V/Vsw: CR801.3, L801.1, U801.2 (Vsw)
GND1: C801.2, C802.2, C803.2, CR801.1, CR801.2, D801.1 (K), R803.2, U801.4 (GND); also elsewhere on the board
unnamed: C802.1, R801.2
unnamed: D801.2 (A), R804.2
unnamed: R802.2, R803.1, U801.5 (FB)
unnamed: R801.1, U801.6 (Vc)

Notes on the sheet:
Reference voltage : VFB = 2.21V

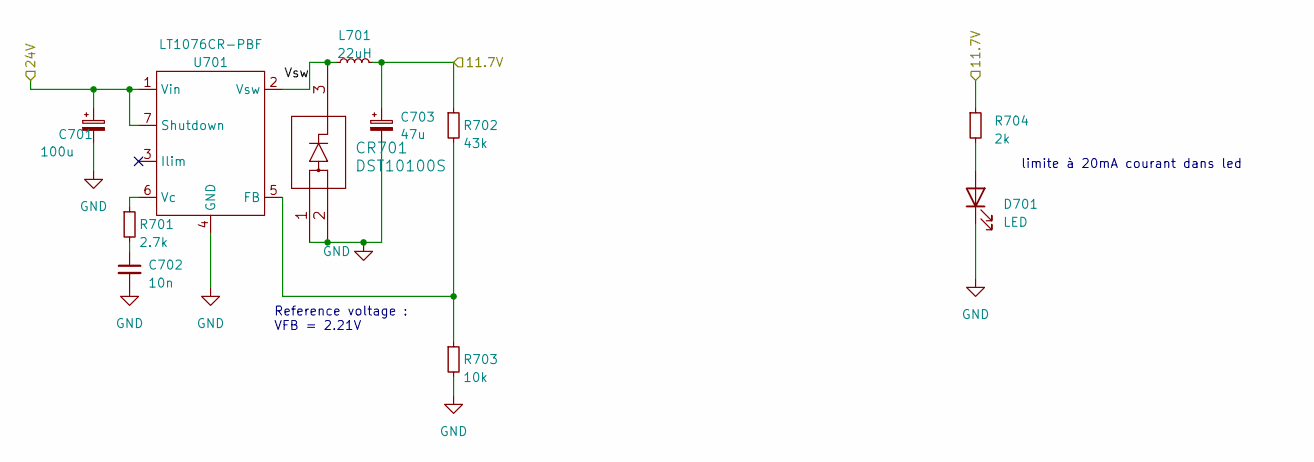
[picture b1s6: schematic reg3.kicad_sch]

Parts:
C701: 100u; CP_Elec_6.3x7.7
C702: 10n; C_0402_1005Metric
C703: 47u; CP_Elec_6.3x5.4
CR701: DST10100S
D701: LED; LED_0603_1608Metric
L701: 22uH; L_Changjiang_FNR8065S
R701: 2.7k; R_0402_1005Metric
R702: 43k; R_0402_1005Metric
R703: 10k; R_0402_1005Metric
R704: 2k; R_0402_1005Metric
U701: LT1076CR-PBF

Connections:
11.7V: C703.1, L701.2, R702.1, R704.1; also elsewhere on the board
24V: C701.1, U701.1 (Vin), U701.7 (Shutdown); also elsewhere on the board
/Régulateur 11.7V/Vsw: CR701.3, L701.1, U701.2 (Vsw)
GND1: C701.2, C702.2, C703.2, CR701.1, CR701.2, D701.1 (K), R703.2, U701.4 (GND); also elsewhere on the board
unnamed: C702.1, R701.2
unnamed: D701.2 (A), R704.2
unnamed: R702.2, R703.1, U701.5 (FB)
unnamed: R701.1, U701.6 (Vc)

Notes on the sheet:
Reference voltage : VFB = 2.21V
limite à 20mA courant dans led

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
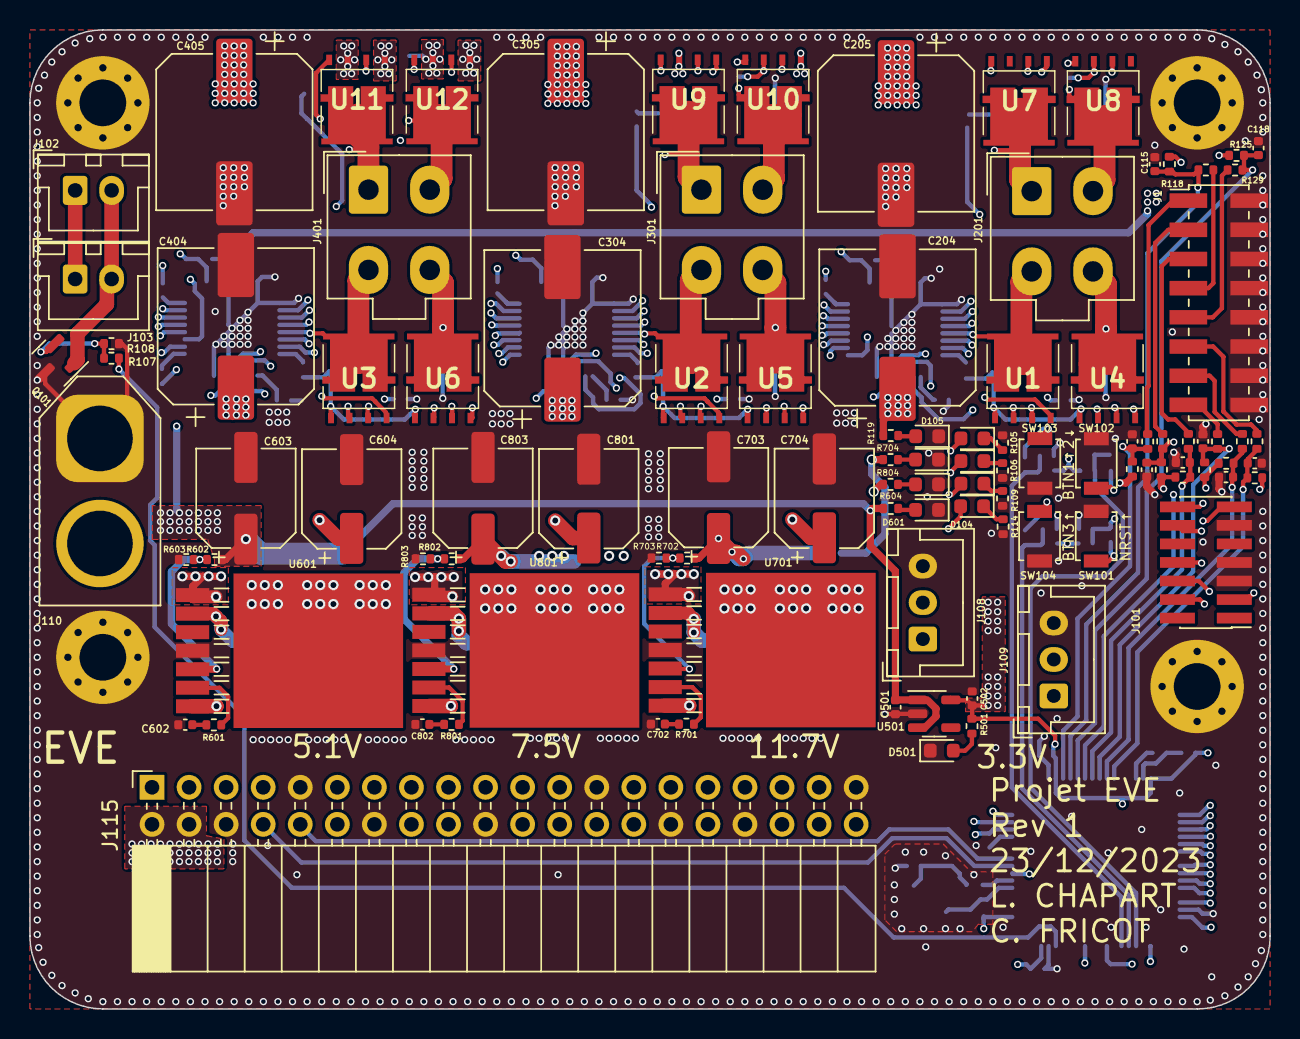
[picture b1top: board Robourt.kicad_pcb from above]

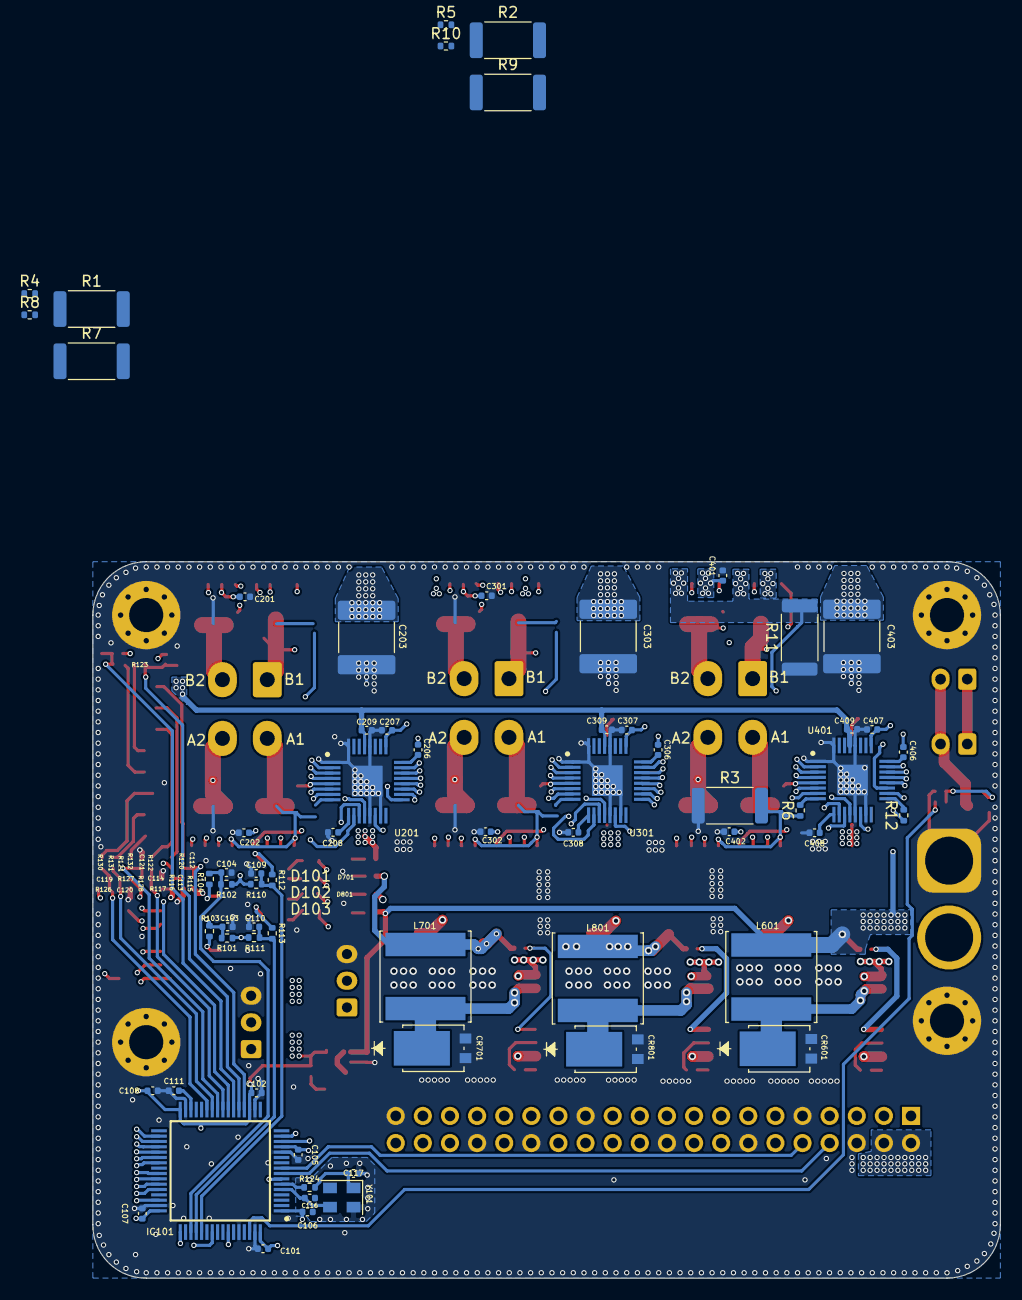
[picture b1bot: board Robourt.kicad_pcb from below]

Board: 4 copper layers, 85.0 x 67.1 mm, 172 parts (66 on the bottom side), 130 nets.

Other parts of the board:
C604, C704: 100u; CP_Elec_6.3x7.7
J1: Conn_02x08_Odd_Even; PinHeader_2x08_P2.00mm_Vertical_SMD
J109: Conn_01x03; JST_XH_B3B-XH-A_1x03_P2.50mm_Vertical
J110: Conn_01x02; AMASS_XT60-F_1x02_P7.20mm_Vertical
J115: Conn_02x20_Odd_Even; PinSocket_2x20_P2.54mm_Horizontal

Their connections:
11.7V: J109.2; also elsewhere on the board
24V: C604.1, C704.1, J110.2; also elsewhere on the board
FDC1: J1.1; also elsewhere on the board
FDC2: J1.3; also elsewhere on the board
FDC3: J1.5; also elsewhere on the board
FDC4: J1.7; also elsewhere on the board
FDC5: J1.9; also elsewhere on the board
FDC6: J1.11; also elsewhere on the board
FDC7: J1.13; also elsewhere on the board
FDC8: J1.15; also elsewhere on the board
GND1: C604.2, C704.2, J1.2, J1.4, J1.6, J1.8, J1.10, J1.12, J1.14, J1.16, J109.3, J110.1, J115.6, J115.9, J115.14, J115.20, J115.25, J115.30, J115.34, J115.39; also elsewhere on the board
LPUART1_RX: J115.8; also elsewhere on the board
LPUART1_TX: J115.10; also elsewhere on the board
USART1_TX: J109.1; also elsewhere on the board

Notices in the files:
parts and their libraries:
Copyright 2021 Accelerated Designs. All rights reserved.
